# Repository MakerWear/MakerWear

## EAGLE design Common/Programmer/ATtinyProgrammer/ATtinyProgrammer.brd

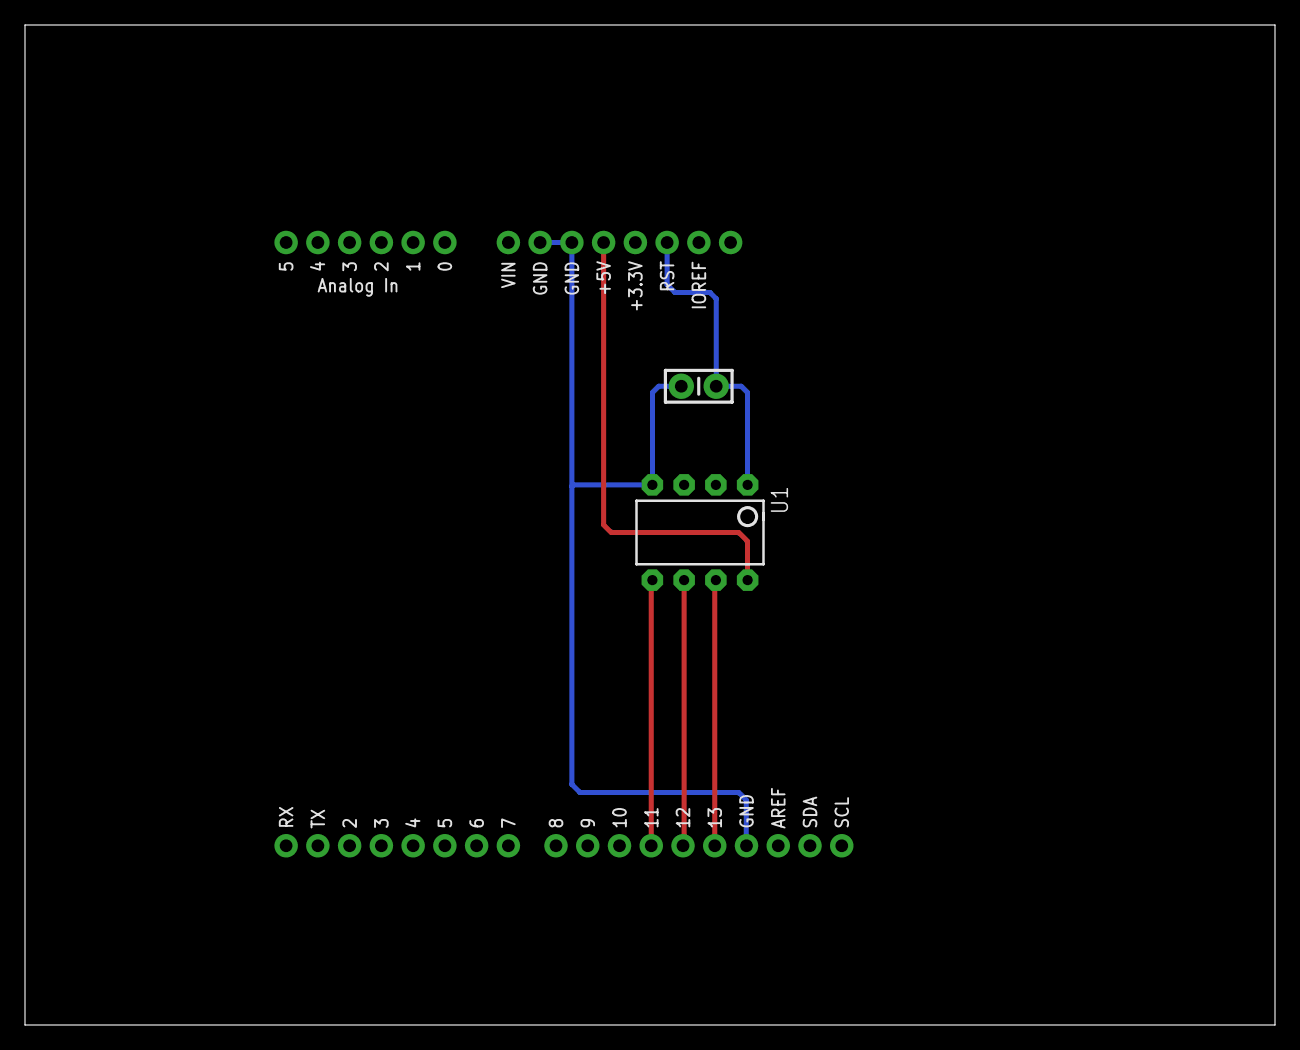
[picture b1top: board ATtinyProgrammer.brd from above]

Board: 2 copper layers, 100.0 x 80.0 mm, 3 parts (0 on the bottom side), 6 nets.

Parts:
C1: 10uF; CAP-PTH-SMALL-KIT
J1: ARDUINO_R3_SHIELD; UNO_R3_SHIELD
U1: TINY85-20-DIP; DIP08

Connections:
GND: C1.2, J1.GND@0, J1.GND@1, J1.GND@2, U1.4
MISO: J1.D12, U1.6
MOSI: J1.D11, U1.5
RES: C1.1, J1.RES, U1.1
SCK: J1.D13, U1.7
VCC: J1.5V, U1.8

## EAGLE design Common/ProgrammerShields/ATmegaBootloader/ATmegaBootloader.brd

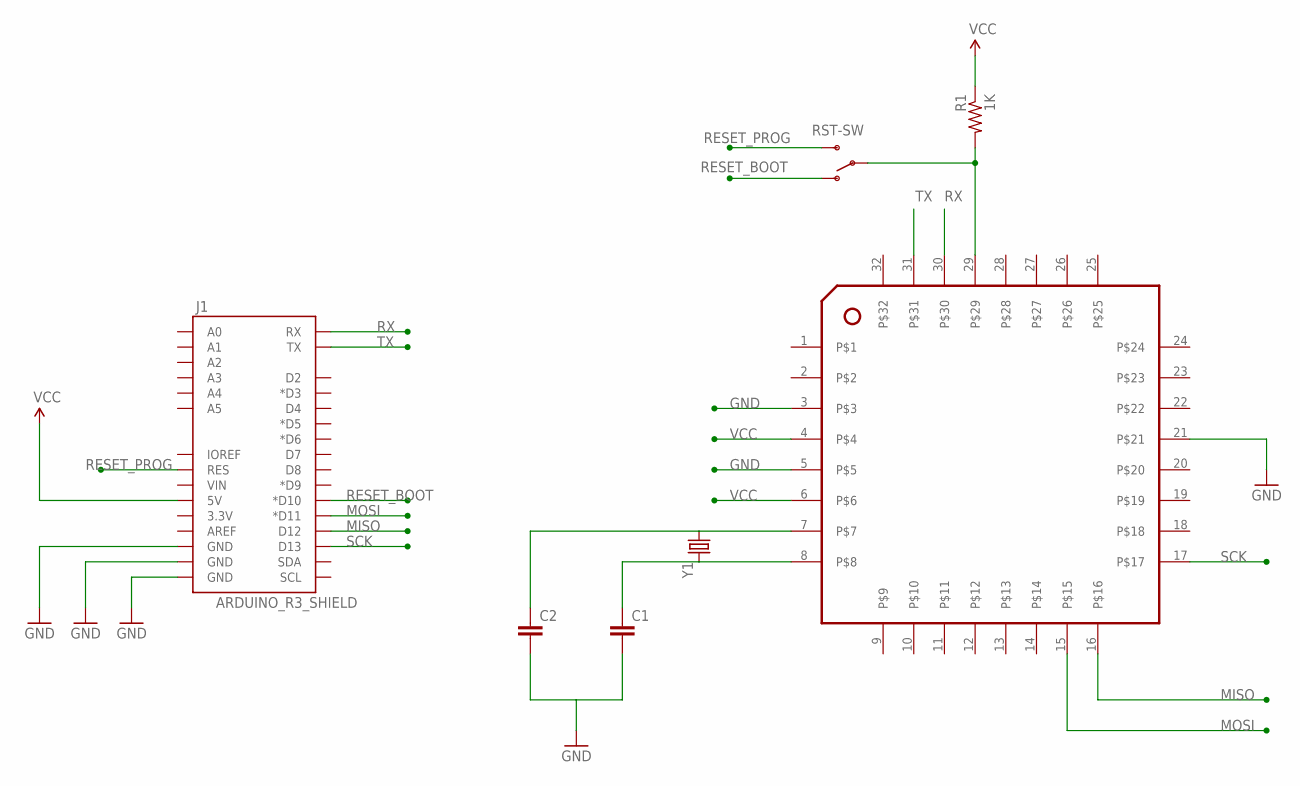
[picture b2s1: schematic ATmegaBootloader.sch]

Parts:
C1, C2: 0.1UF-50V-20%(PTH)KIT-EZ; CAP-PTH-SMALL-KIT
J1: ARDUINO_R3_SHIELD; UNO_R3_SHIELD
R1: 1K; AXIAL-0.3
RST-SW: SWITCH-SPDTPTH; SWITCH-SPDT
U$1: ATMEGA-TQFP-BREAKOUT; TQFP32-BREAKOUT
Y1: CRYSTALHC49US; HC49US

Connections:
GND: C1.2, C2.2, J1.GND@0 (GND), J1.GND@1 (GND), J1.GND@2 (GND), U$1.3, U$1.5, U$1.21
MISO: J1.D12, U$1.16
MOSI: J1.D11 (*D11), U$1.15
unnamed: C2.1, U$1.7, Y1.1
unnamed: C1.1, U$1.8, Y1.2
RESET: R1.P$2 (2), RST-SW.2, U$1.29
RESET_BOOT: J1.D10 (*D10), RST-SW.1 (O)
RESET_PROG: J1.RES, RST-SW.3 (S)
RX: J1.RX, U$1.30
SCK: J1.D13, U$1.17
TX: J1.TX, U$1.31
VCC: J1.5V, R1.P$1 (1), U$1.4, U$1.6

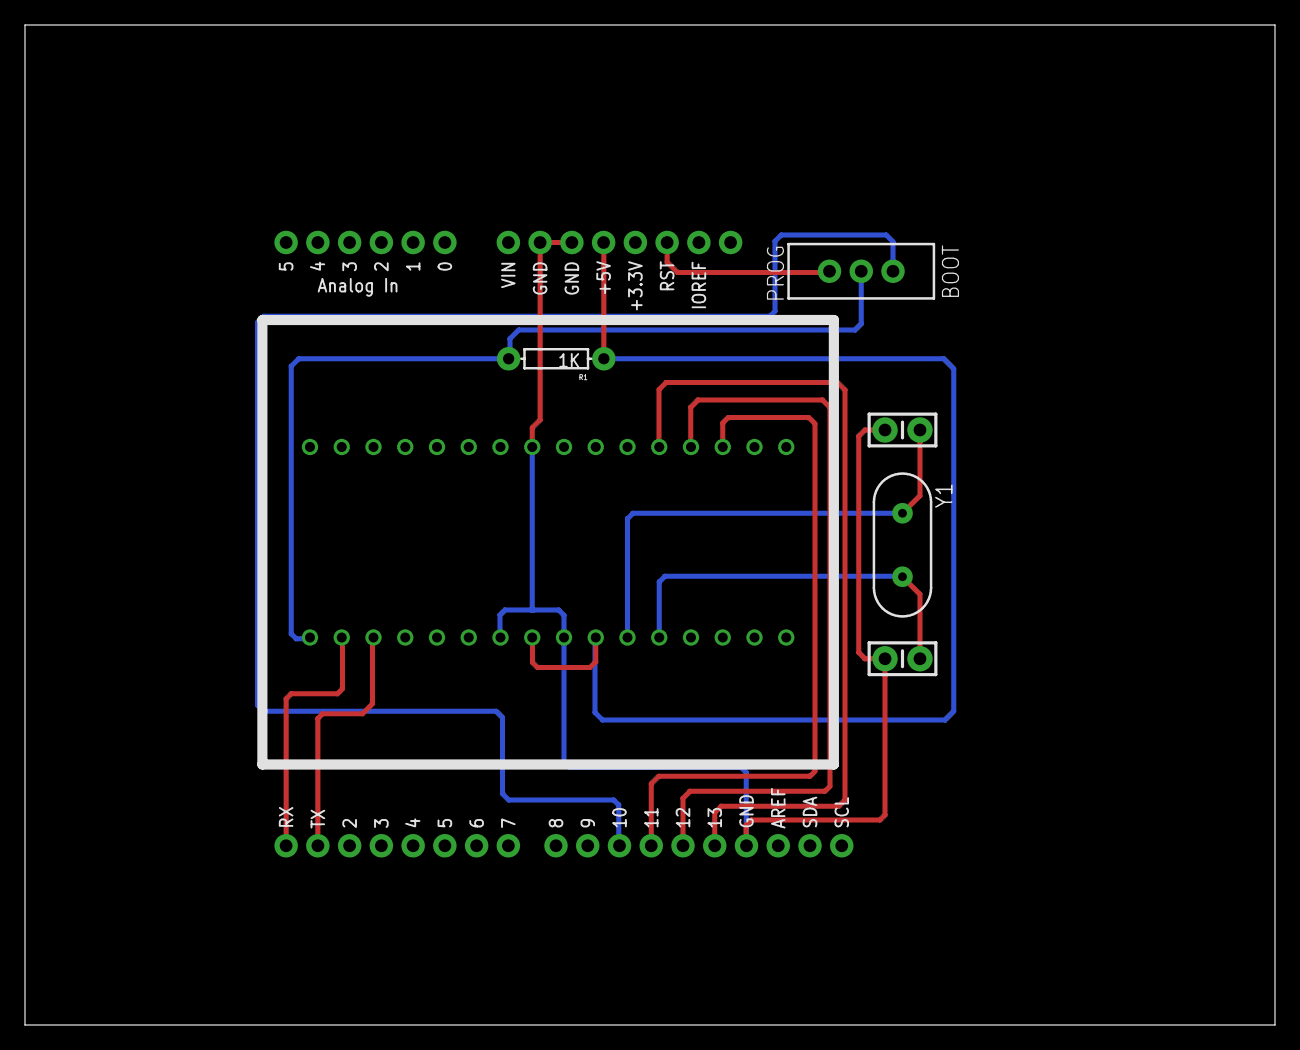
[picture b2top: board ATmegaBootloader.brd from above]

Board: 2 copper layers, 100.0 x 80.0 mm, 7 parts (0 on the bottom side), 12 nets.

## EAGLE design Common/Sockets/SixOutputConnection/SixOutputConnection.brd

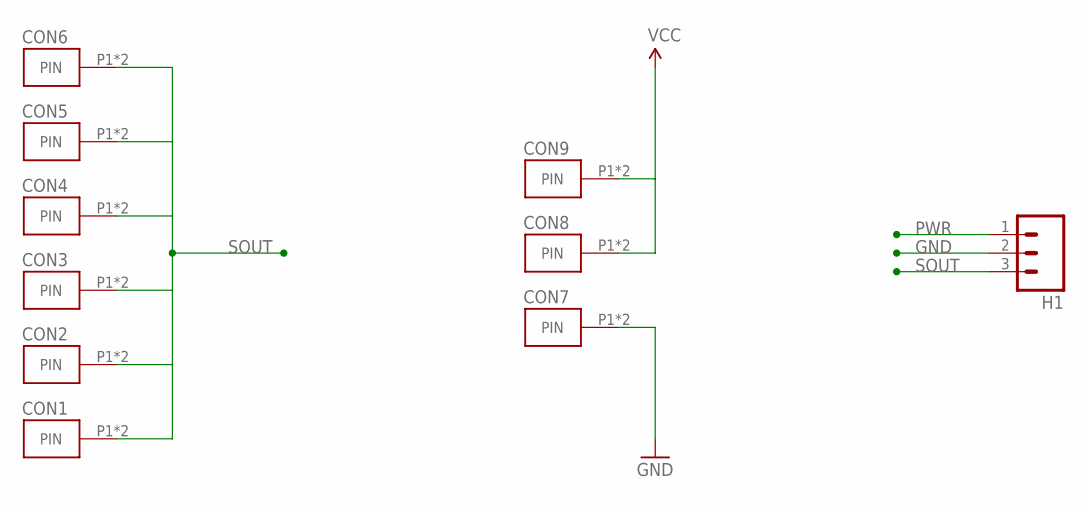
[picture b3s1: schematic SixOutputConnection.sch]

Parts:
CON1, CON2, CON3, CON4, CON5, CON6, CON7, CON8, CON9: SHIELD_FINGER0820; SHIELD_FINGER_PKG
H1: M031X03_NO_HOLES; 1X03_NO_HOLES

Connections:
GND: CON7.P1, CON7.P2, H1.2
PWR: CON8.P1, CON8.P2, CON9.P1, CON9.P2, H1.1
SOUT: CON1.P1, CON1.P2, CON2.P1, CON2.P2, CON3.P1, CON3.P2, CON4.P1, CON4.P2, CON5.P1, CON5.P2, CON6.P1, CON6.P2, H1.3

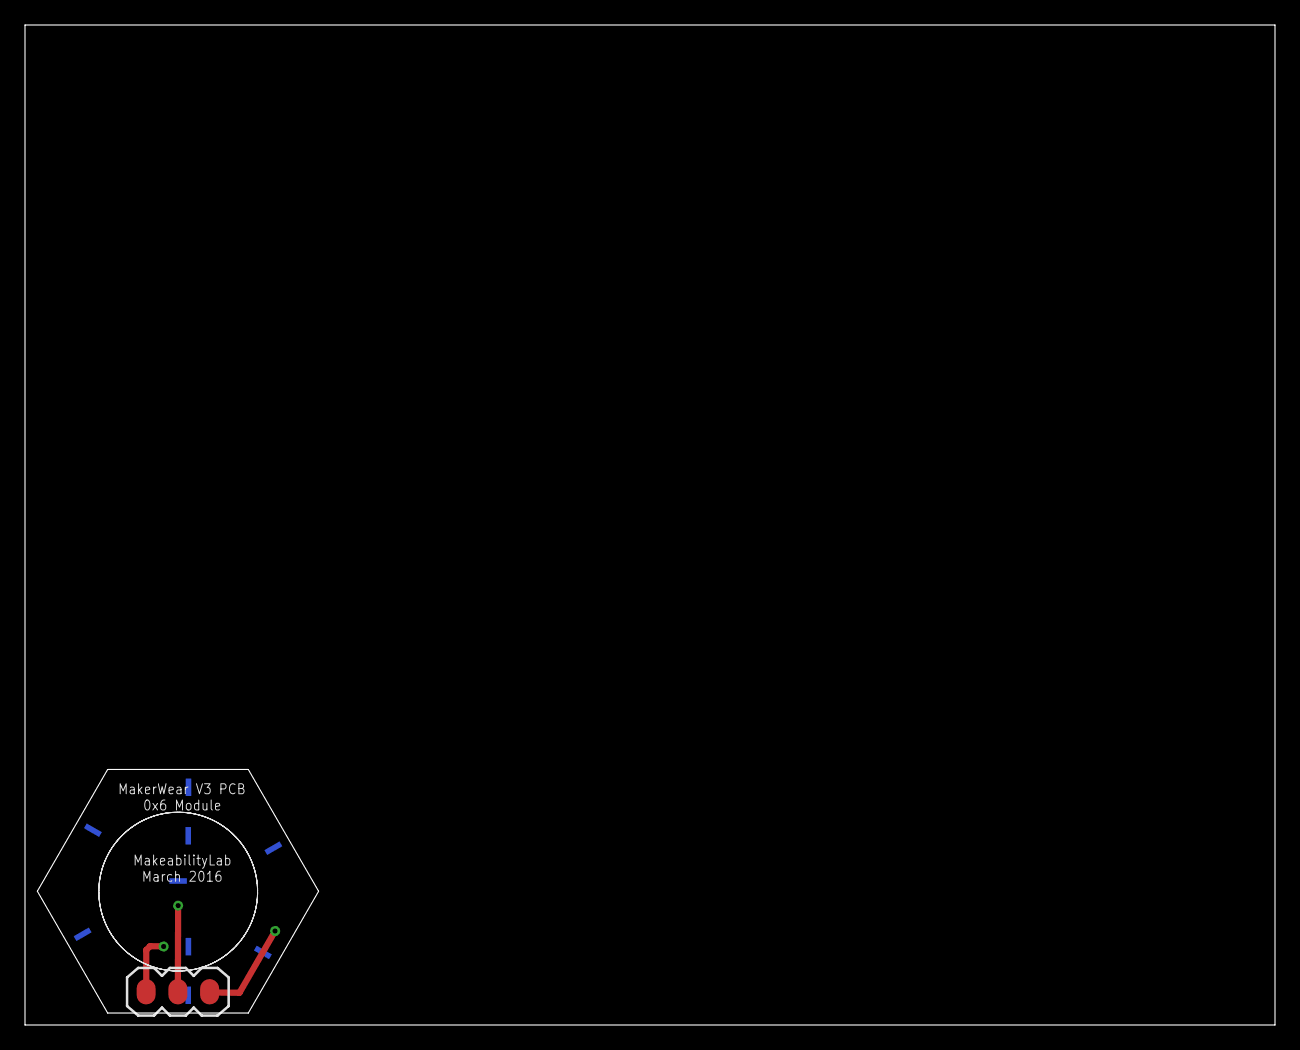
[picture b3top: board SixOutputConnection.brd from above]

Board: 2 copper layers, 100.0 x 80.0 mm, 10 parts (0 on the bottom side), 3 nets.

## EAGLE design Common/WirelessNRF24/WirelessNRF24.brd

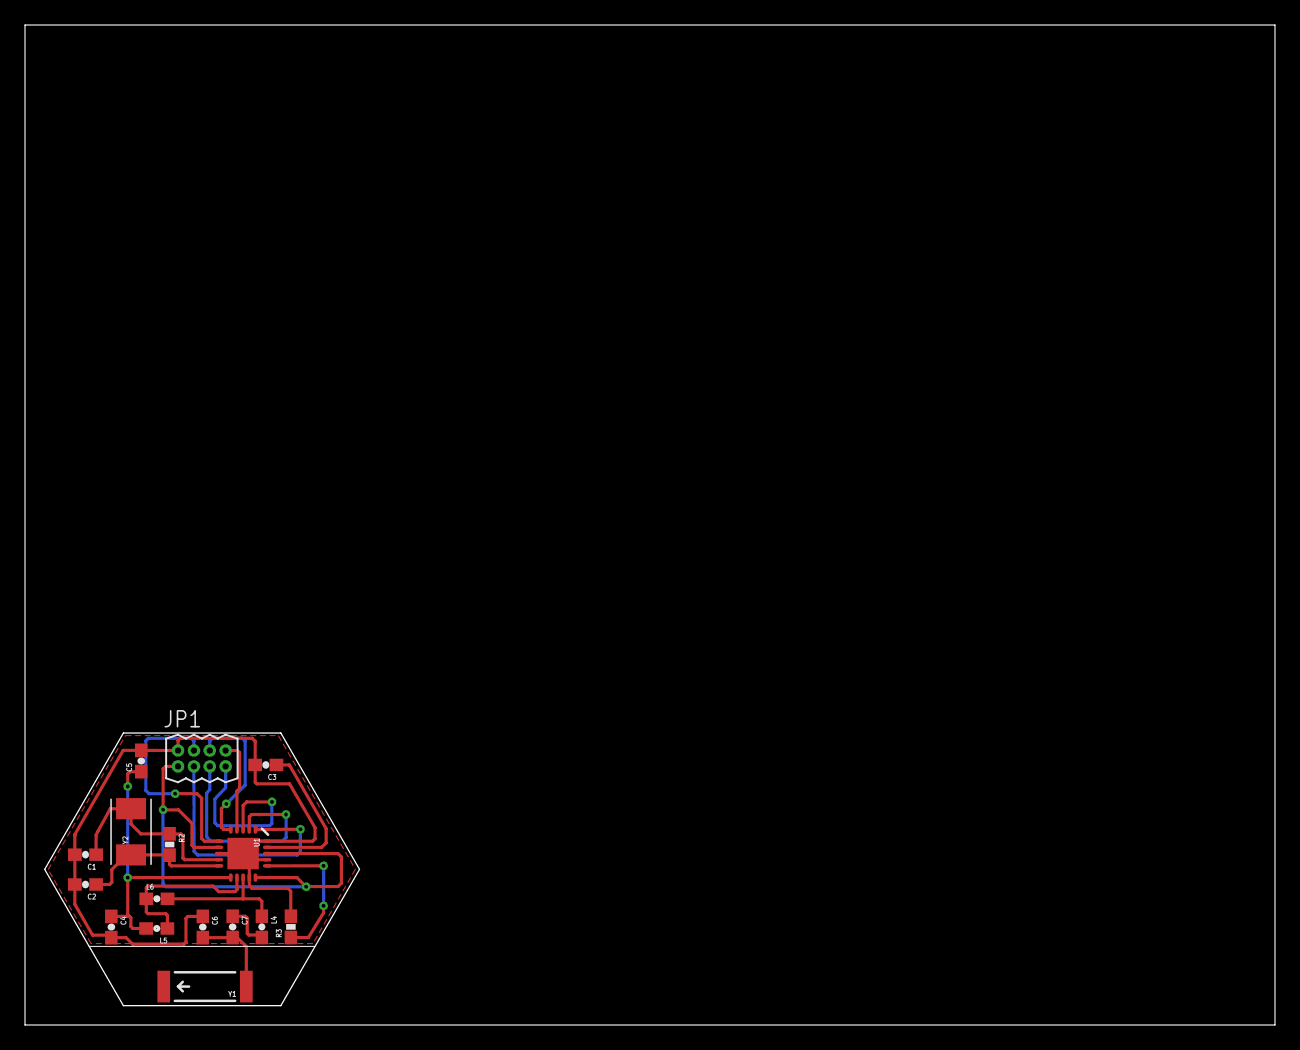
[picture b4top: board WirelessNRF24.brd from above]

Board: 2 copper layers, 100.0 x 80.0 mm, 16 parts (0 on the bottom side), 17 nets.

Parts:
C1, C2: 22pF; 0603-CAP
C3: 33nF; 0603-CAP
C4: 2.2nF; 0603-CAP
C5: 4.7pF; 0603-CAP
C6: 1.0pF; 0603-CAP
C7: 1.5pF; 0603-CAP
JP1: M04X2_0.05"
L4: 3.9nH; 0603
L5: 2.7nH; 0603
L6: 8.2nH; 0603
R2: 1M; 0603-RES
R3: 22K; 0603-RES
U1: NRF24L01ALT1; QFN20_ALT1
Y1: ANTENNA2SMD5; ANTENNA-CHIP5
Y2: 16MHz; CRYSTAL-TXC-7A

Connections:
ANT: C6.2, C7.2, Y1.FEED
CE: JP1.3, U1.1
CSN: JP1.5, U1.2
GND: C1.2, C2.2, C3.2, C4.2, C5.2, C6.1, JP1.2, R3.2, U1.0, U1.8, U1.14, U1.17, U1.20
IRQ: JP1.4, U1.6
MISO: JP1.6, U1.5
MOSI: JP1.8, U1.4
unnamed: C1.1, R2.1, U1.9, Y2.P$1
unnamed: C2.1, R2.2, U1.10, Y2.P$2
unnamed: L5.1, L6.1, U1.12
unnamed: R3.1, U1.16
unnamed: C3.1, U1.19
unnamed: L4.1, L6.2, U1.13
unnamed: C4.1, C5.1, L5.2, U1.11
unnamed: C7.1, L4.2
SCK: JP1.7, U1.3
VCC: JP1.1, U1.7, U1.15, U1.18

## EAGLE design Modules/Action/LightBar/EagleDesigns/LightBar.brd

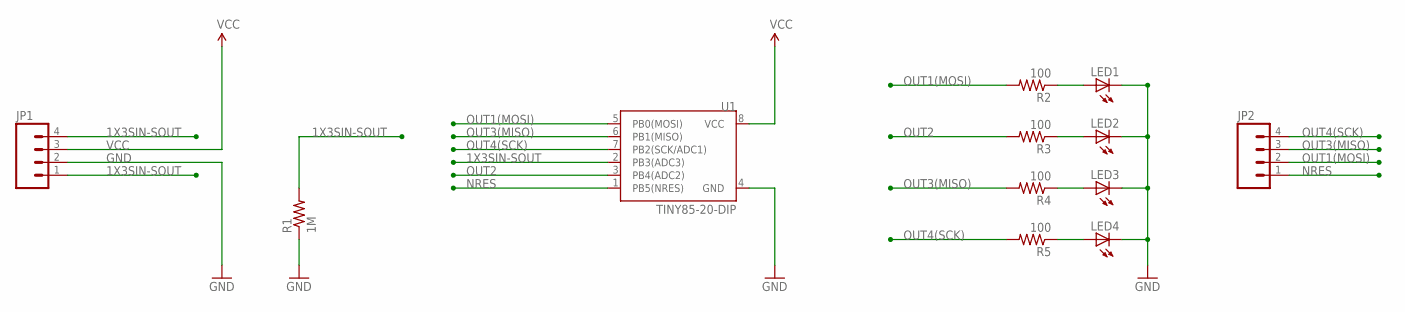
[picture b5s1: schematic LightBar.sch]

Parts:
JP1, JP2: M04PTH; 1X04
LED1, LED2, LED3, LED4: LEDSQR2X5; LED2X5
R1: 1M; R0603
R2, R3, R4, R5: 100; R0603
U1: TINY85-20-DIP; DIP08

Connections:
1X3SIN-SOUT: JP1.1, JP1.4, R1.2, U1.2 (PB3(ADC3))
GND: JP1.2, LED1.K (C), LED2.K (C), LED3.K (C), LED4.K (C), R1.1, U1.4 (GND)
unnamed: LED1.A, R2.1
unnamed: LED2.A, R3.1
unnamed: LED3.A, R4.1
unnamed: LED4.A, R5.1
NRES: JP2.1, U1.1 (PB5(NRES))
OUT1(MOSI): JP2.2, R2.2, U1.5 (PB0(MOSI))
OUT2: R3.2, U1.3 (PB4(ADC2))
OUT3(MISO): JP2.3, R4.2, U1.6 (PB1(MISO))
OUT4(SCK): JP2.4, R5.2, U1.7 (PB2(SCK/ADC1))
VCC: JP1.3, U1.8 (VCC)

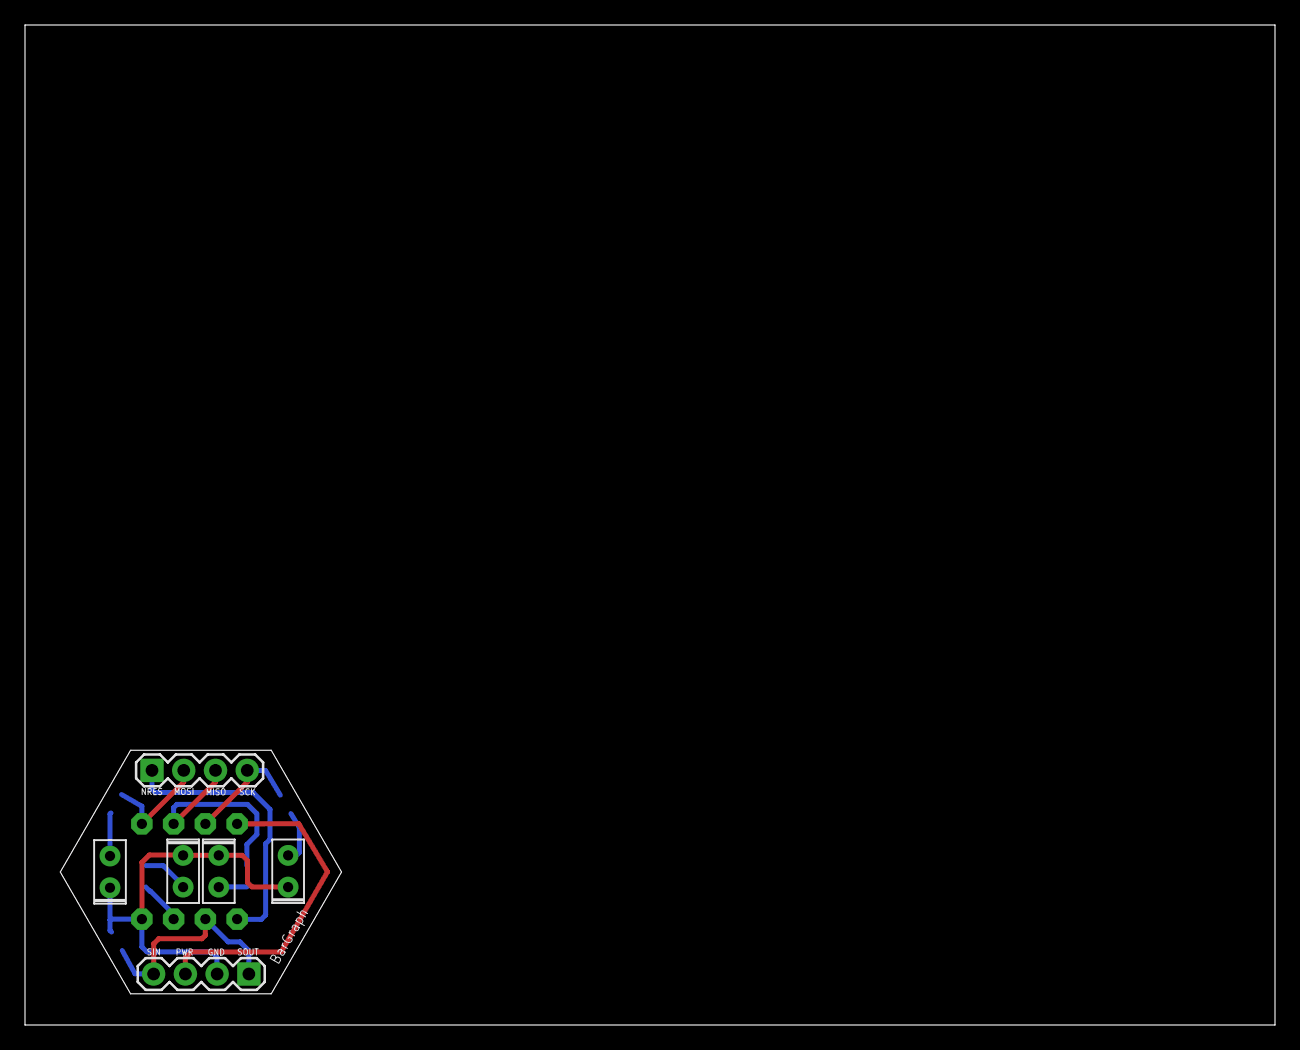
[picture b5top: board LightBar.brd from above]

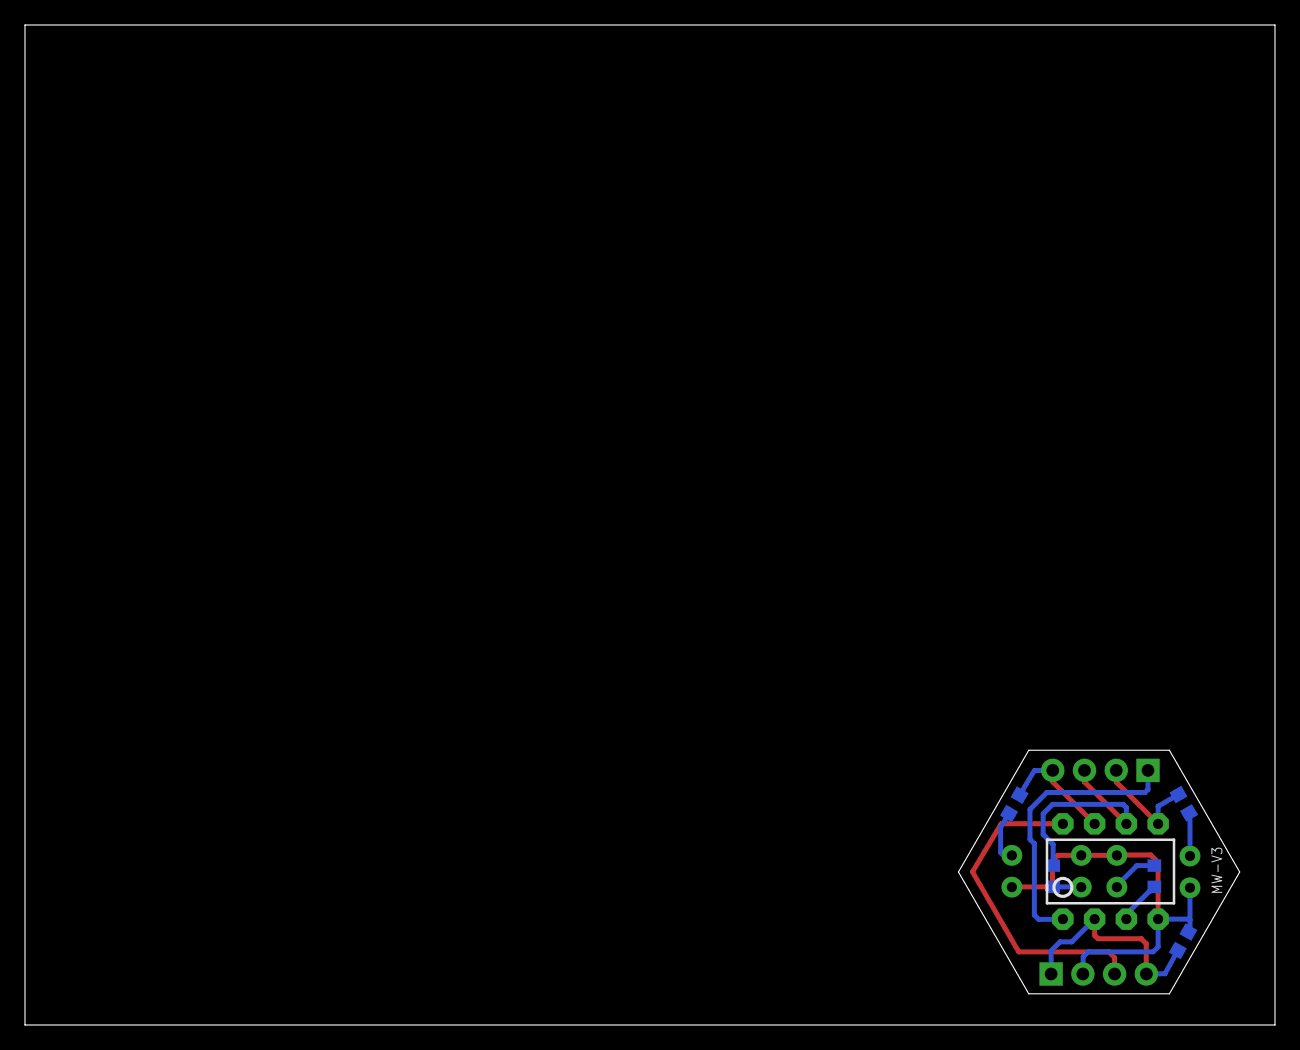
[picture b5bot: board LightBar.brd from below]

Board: 2 copper layers, 100.0 x 80.0 mm, 12 parts (6 on the bottom side), 12 nets.

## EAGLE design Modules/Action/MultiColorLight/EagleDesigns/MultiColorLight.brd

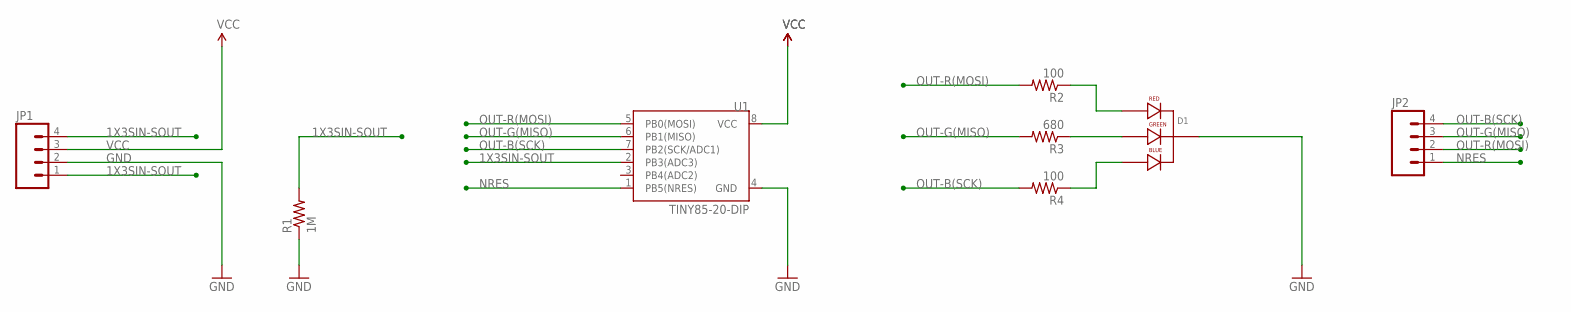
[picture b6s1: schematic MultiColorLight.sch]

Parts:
D1: LED-RGB-CC-THRUCLEAR; LED-RGB-THRU
JP1, JP2: M04PTH; 1X04
R1: 1M; R0603
R2, R4: 100; R0603
R3: 680; R0603
U1: TINY85-20-DIP; DIP08

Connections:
1X3SIN-SOUT: JP1.1, JP1.4, R1.2, U1.2 (PB3(ADC3))
GND: D1.2 (CATHODE), JP1.2, R1.1, U1.4 (GND)
unnamed: D1.1 (RED_CATHODE), R2.1
unnamed: D1.3 (GREEN_CATHODE), R3.1
unnamed: D1.4 (BLUE_CATHODE), R4.1
NRES: JP2.1, U1.1 (PB5(NRES))
OUT-B(SCK): JP2.4, R4.2, U1.7 (PB2(SCK/ADC1))
OUT-G(MISO): JP2.3, R3.2, U1.6 (PB1(MISO))
OUT-R(MOSI): JP2.2, R2.2, U1.5 (PB0(MOSI))
VCC: JP1.3, U1.8 (VCC)

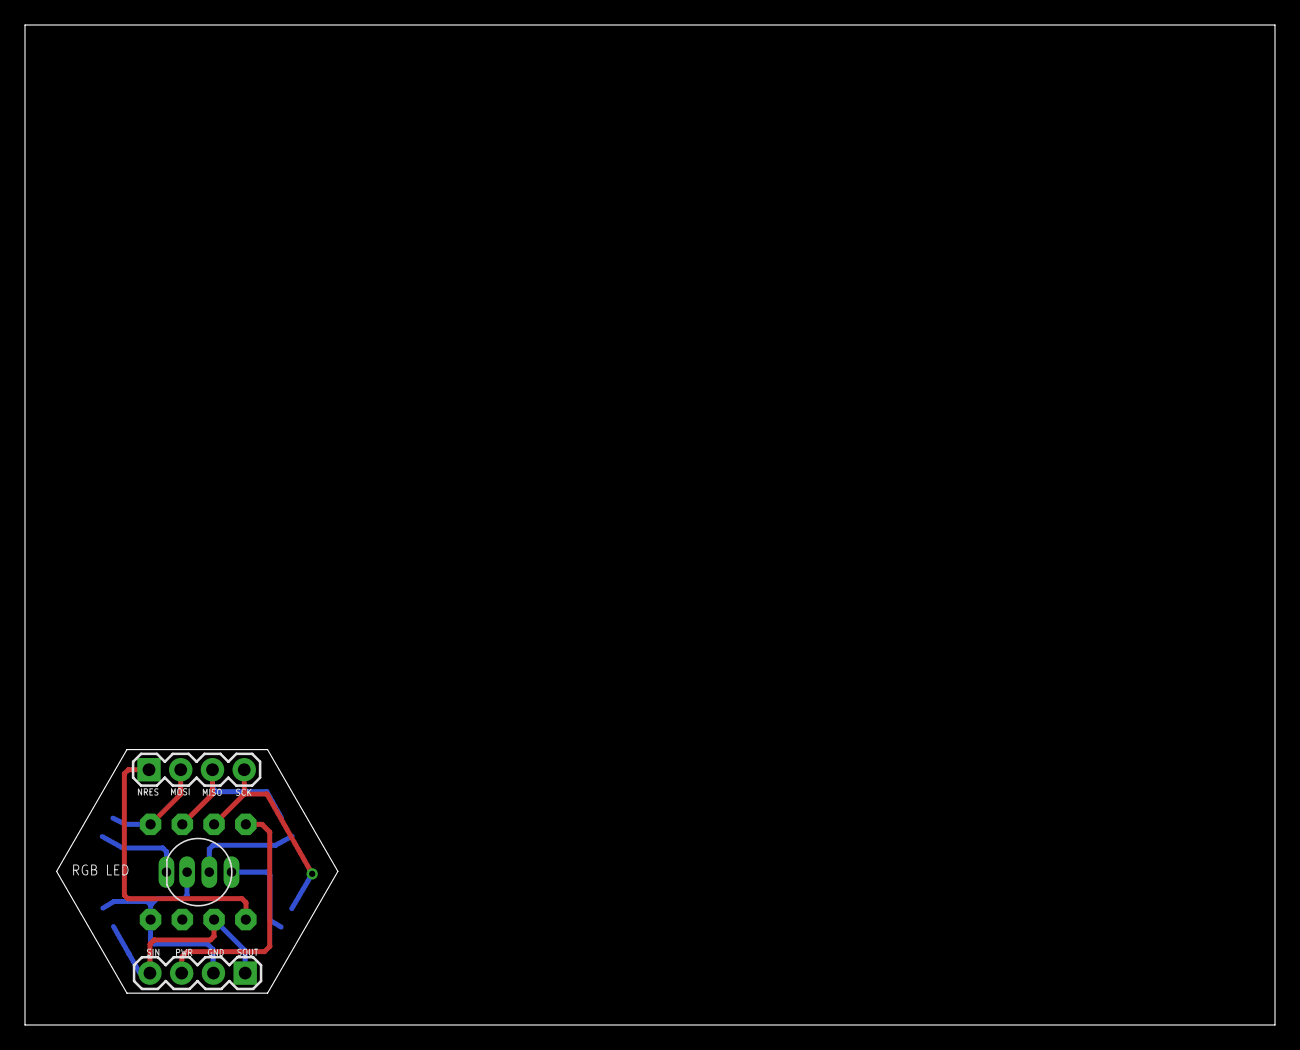
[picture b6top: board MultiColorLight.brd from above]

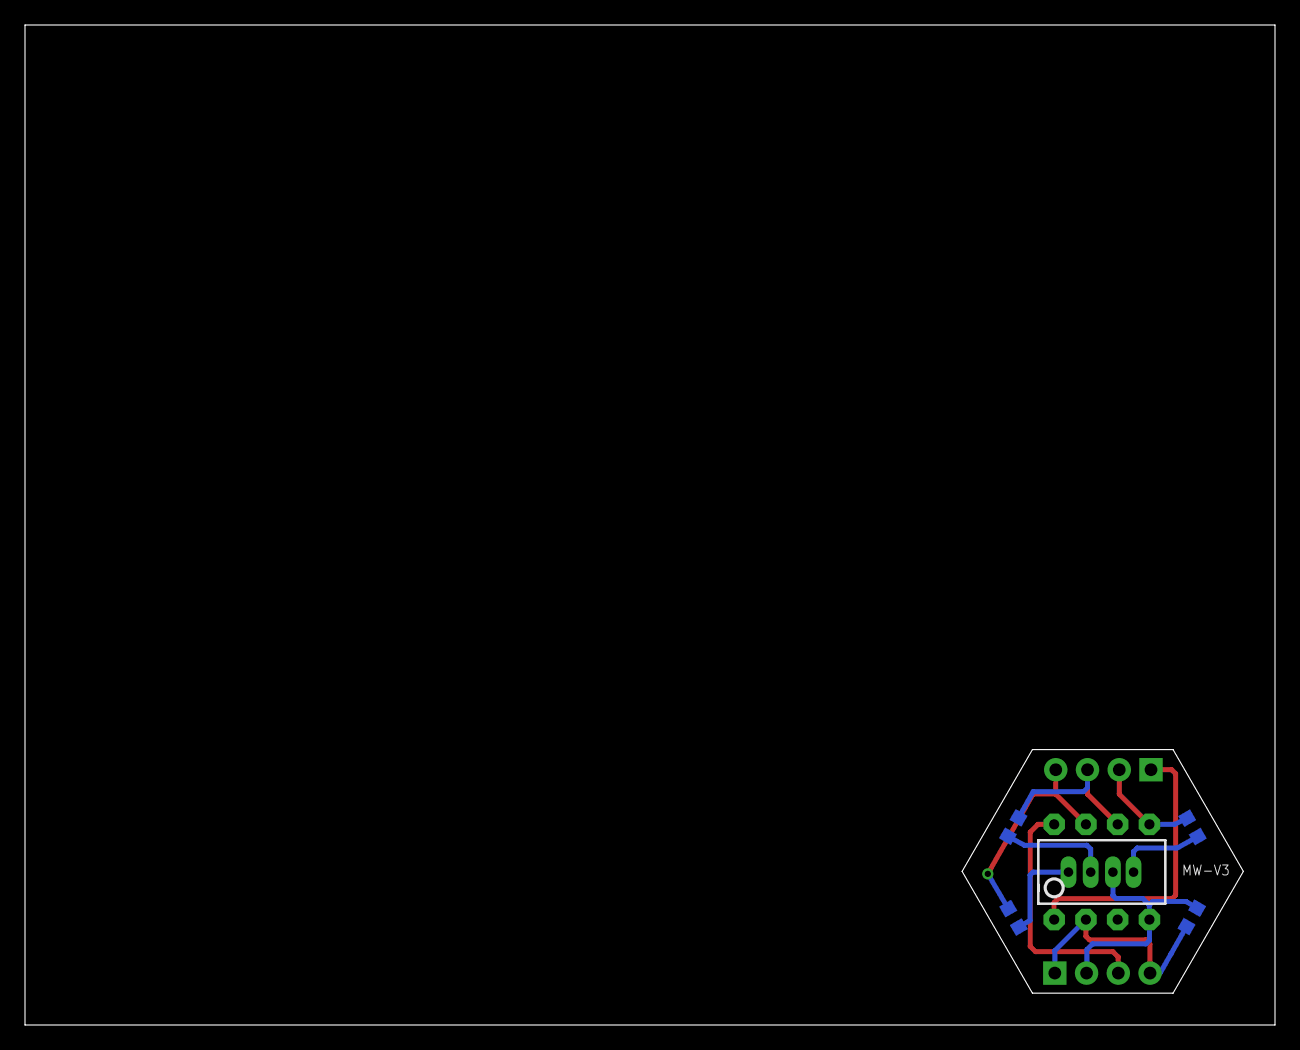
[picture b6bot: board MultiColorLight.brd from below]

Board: 2 copper layers, 100.0 x 80.0 mm, 8 parts (5 on the bottom side), 10 nets.

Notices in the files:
parts and their libraries:
SparkFun-Boards: Licensing: Creative Commons ShareAlike 4.0 International - https://creativecommons.org/licenses/by-sa/4.0
